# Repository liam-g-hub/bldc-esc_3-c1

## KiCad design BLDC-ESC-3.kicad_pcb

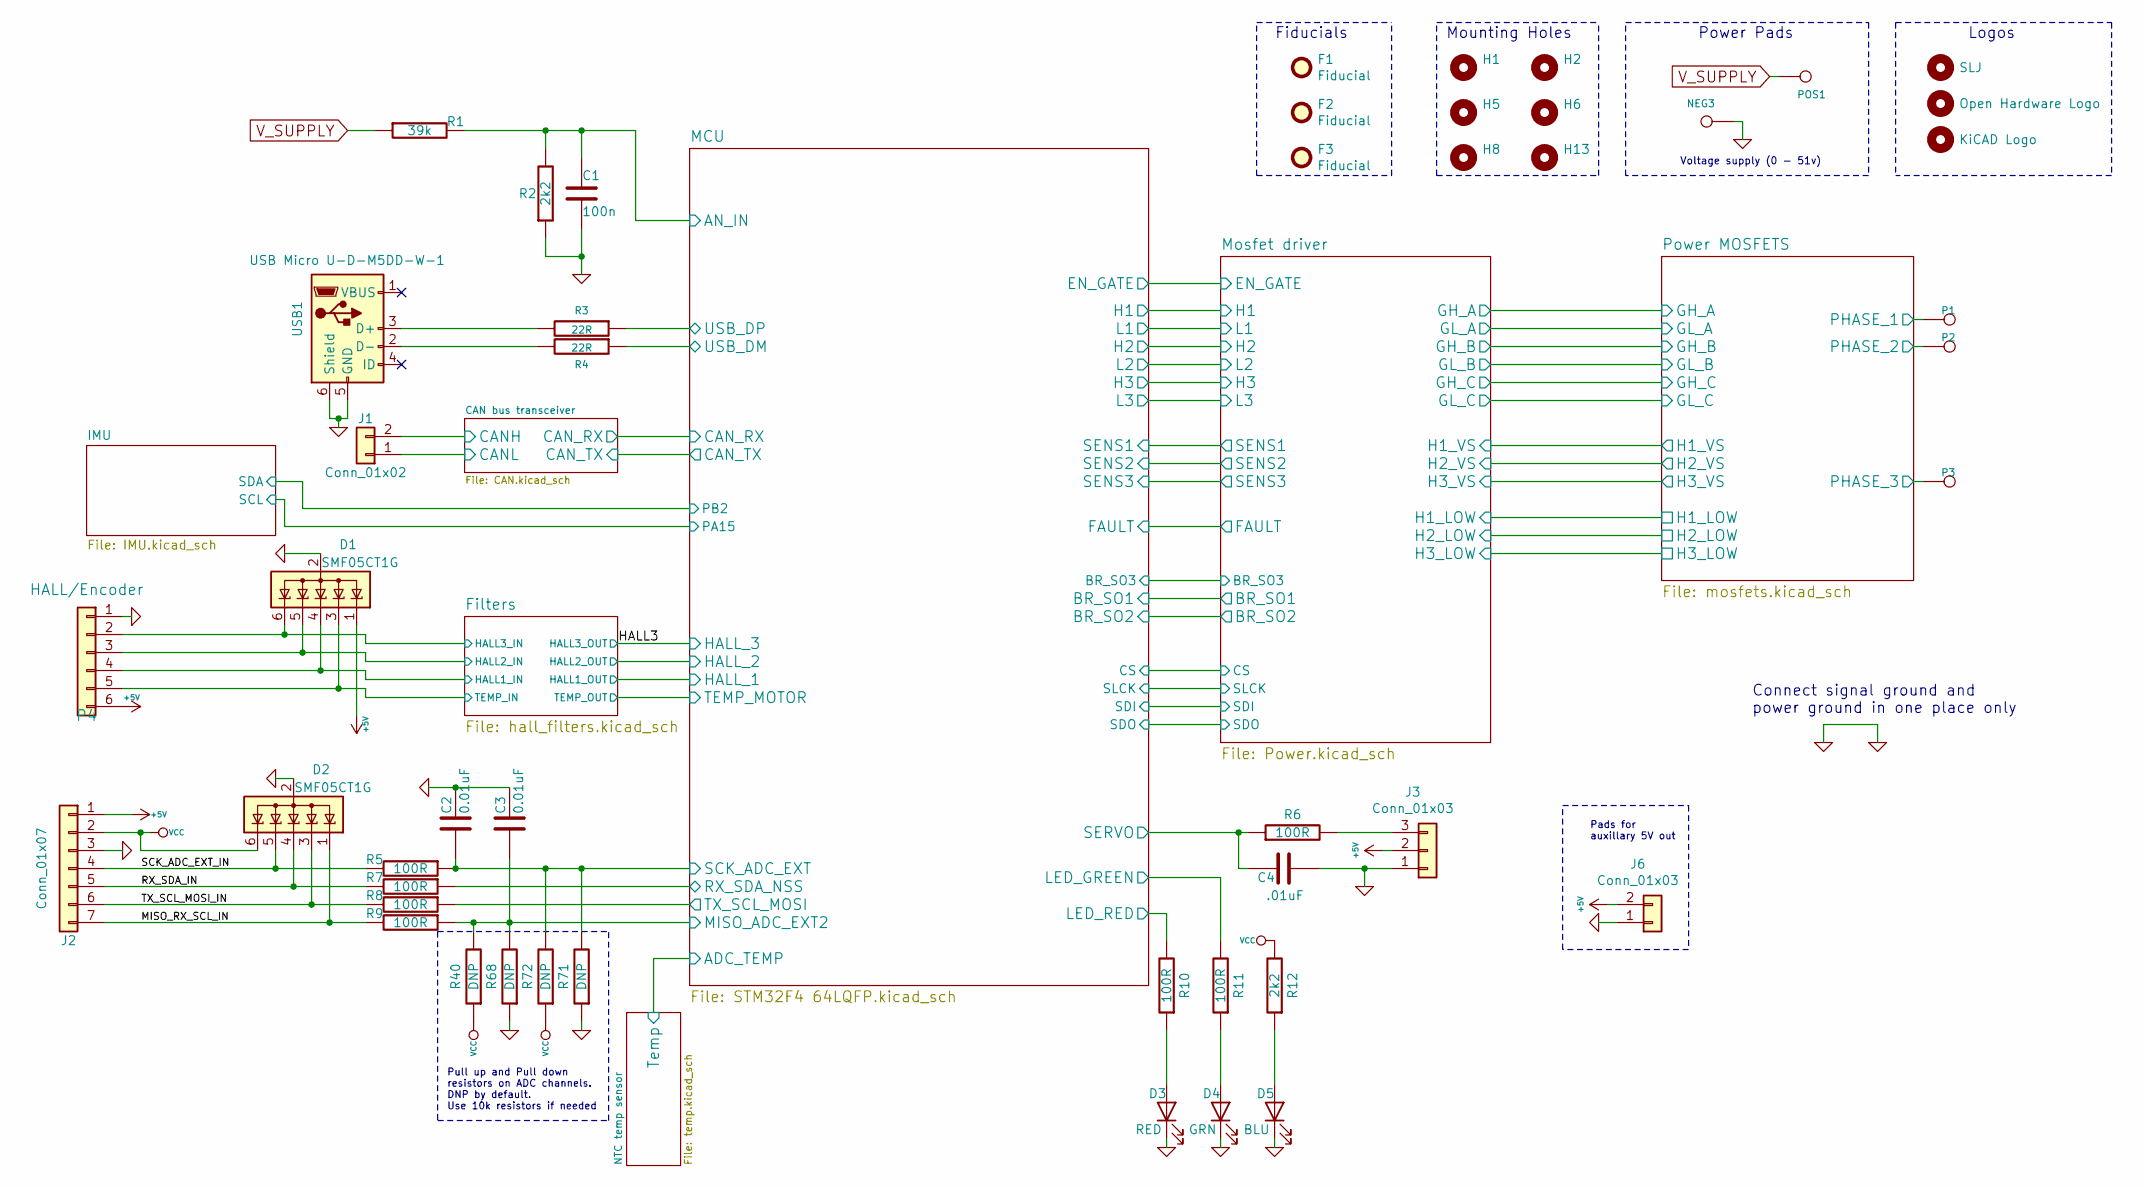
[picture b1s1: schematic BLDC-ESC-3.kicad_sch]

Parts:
C1: 100n; C_0603_1608Metric
C2, C3: 0.01uF; C_0603_1608Metric
C4: .01uF; C_0603_1608Metric
D1, D2: SMF05CT1G; SOT-363_SC-70-6
D3: RED; LED_0603_1608Metric
D4: GRN; LED_0603_1608Metric
D5: BLU; LED_0603_1608Metric
F1, F2, F3: Fiducial; Fiducial_1mm_Dia_2mm_Outer
H1, H2, H5, H6, H8, H13: MountingHole; MountingHole_3.2mm_M3_ISO14580_Pad
H3: SLJ; Sam_J
H4: Open Hardware Logo; OSHW-Logo2_9.8x8mm_SilkScreen
H9: KiCAD Logo; KiCad-Logo2_5mm_SilkScreen
J1: Conn_01x02; JST_PH_B2B-PH-K_1x02_P2.00mm_Vertical
J2: Conn_01x07; JST_PH_B7B-PH-K_1x07_P2.00mm_Vertical
J3: Conn_01x03; JST_PH_B3B-PH-K_1x03_P2.00mm_Vertical_hybrid
J6: Conn_01x03; PinHeader_1x02_P2.54mm_Vertical
NEG3: MOTOR3; 1pin_4mm
P1, P2, P3: MOTOR1; 1pin_4mm
P4: HALL/Encoder; JST_PH_B6B-PH-K_1x06_P2.00mm_Vertical
POS1: POS; 1pin_4mm
R1: 39k; R_0603_1608Metric
R2, R12: 2k2; R_0603_1608Metric
R3, R4: 22R; R_0603_1608Metric
R5, R6, R7, R8, R9, R10, R11: 100R; R_0603_1608Metric
R40, R68, R71, R72: DNP; R_0603_1608Metric
USB1: USB Micro U-D-M5DD-W-1; USB_Micro-B_Wuerth_614105150721_Vertical

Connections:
+5V: D1.1 (K), J2.1, J3.2, J6.2, P4.6; also elsewhere on the board
/CAN bus transceiver/CANH: J1.2; also elsewhere on the board
/CAN bus transceiver/CANL: J1.1; also elsewhere on the board
/Filters/HALL1_IN: D1.4 (K), P4.4; also elsewhere on the board
/Filters/HALL2_IN: D1.5 (K), P4.3; also elsewhere on the board
/Filters/HALL3_IN: D1.6 (K), P4.2; also elsewhere on the board
/Filters/TEMP_IN: D1.3 (K), P4.5; also elsewhere on the board
/MCU/AN_IN: C1.2, R1.2, R2.2; also elsewhere on the board
/MCU/LED_GREEN: R11.2; also elsewhere on the board
/MCU/LED_RED: R10.2; also elsewhere on the board
/MCU/MISO_ADC_EXT2: C3.2, R9.1, R40.2, R68.2; also elsewhere on the board
/MCU/RX_SDA_NSS: R7.1; also elsewhere on the board
/MCU/SCK_ADC_EXT: C2.2, R5.1, R71.2, R72.2; also elsewhere on the board
/MCU/SERVO: C4.2, R6.1; also elsewhere on the board
/MCU/TX_SCL_MOSI: R8.1; also elsewhere on the board
/MCU/USB_DM: R4.1; also elsewhere on the board
/MCU/USB_DP: R3.1; also elsewhere on the board
/MISO_RX_SCL_IN: D2.1 (K), J2.7, R9.2
/Mosfet driver/H1_VS: P1.1; also elsewhere on the board
/Mosfet driver/H2_VS: P2.1; also elsewhere on the board
/Mosfet driver/H3_VS: P3.1; also elsewhere on the board
/RX_SDA_IN: D2.4 (K), J2.5, R7.2
/SCK_ADC_EXT_IN: D2.5 (K), J2.4, R5.2
/TX_SCL_MOSI_IN: D2.3 (K), J2.6, R8.2
GND: C1.1, C2.1, C3.1, C4.1, D1.2 (A), D2.2 (A), D3.1 (K), D4.1 (K), D5.1 (K), J2.3, J3.1, J6.1, NEG3.1, P4.1, R2.1, R68.1, R71.1, USB1.5 (GND), USB1.6 (Shield); also elsewhere on the board
unnamed: D3.2 (A), R10.1
unnamed: D4.2 (A), R11.1
unnamed: D5.2 (A), R12.1
unnamed: J3.3, R6.2
unnamed: R3.2, USB1.3 (D+)
unnamed: R4.2, USB1.2 (D-)
VCC: D2.6 (K), J2.2, R12.2, R40.1, R72.1; also elsewhere on the board
V_SUPPLY: POS1.1, R1.1; also elsewhere on the board

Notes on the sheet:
Pull up and Pull down resistors on ADC channels. DNP by default. Use 10k resistors if needed
Voltage supply (0 - 51v)
Mounting Holes
Power Pads
Pads for auxillary 5V out
Logos
Connect signal ground and power ground in one place only
Fiducials

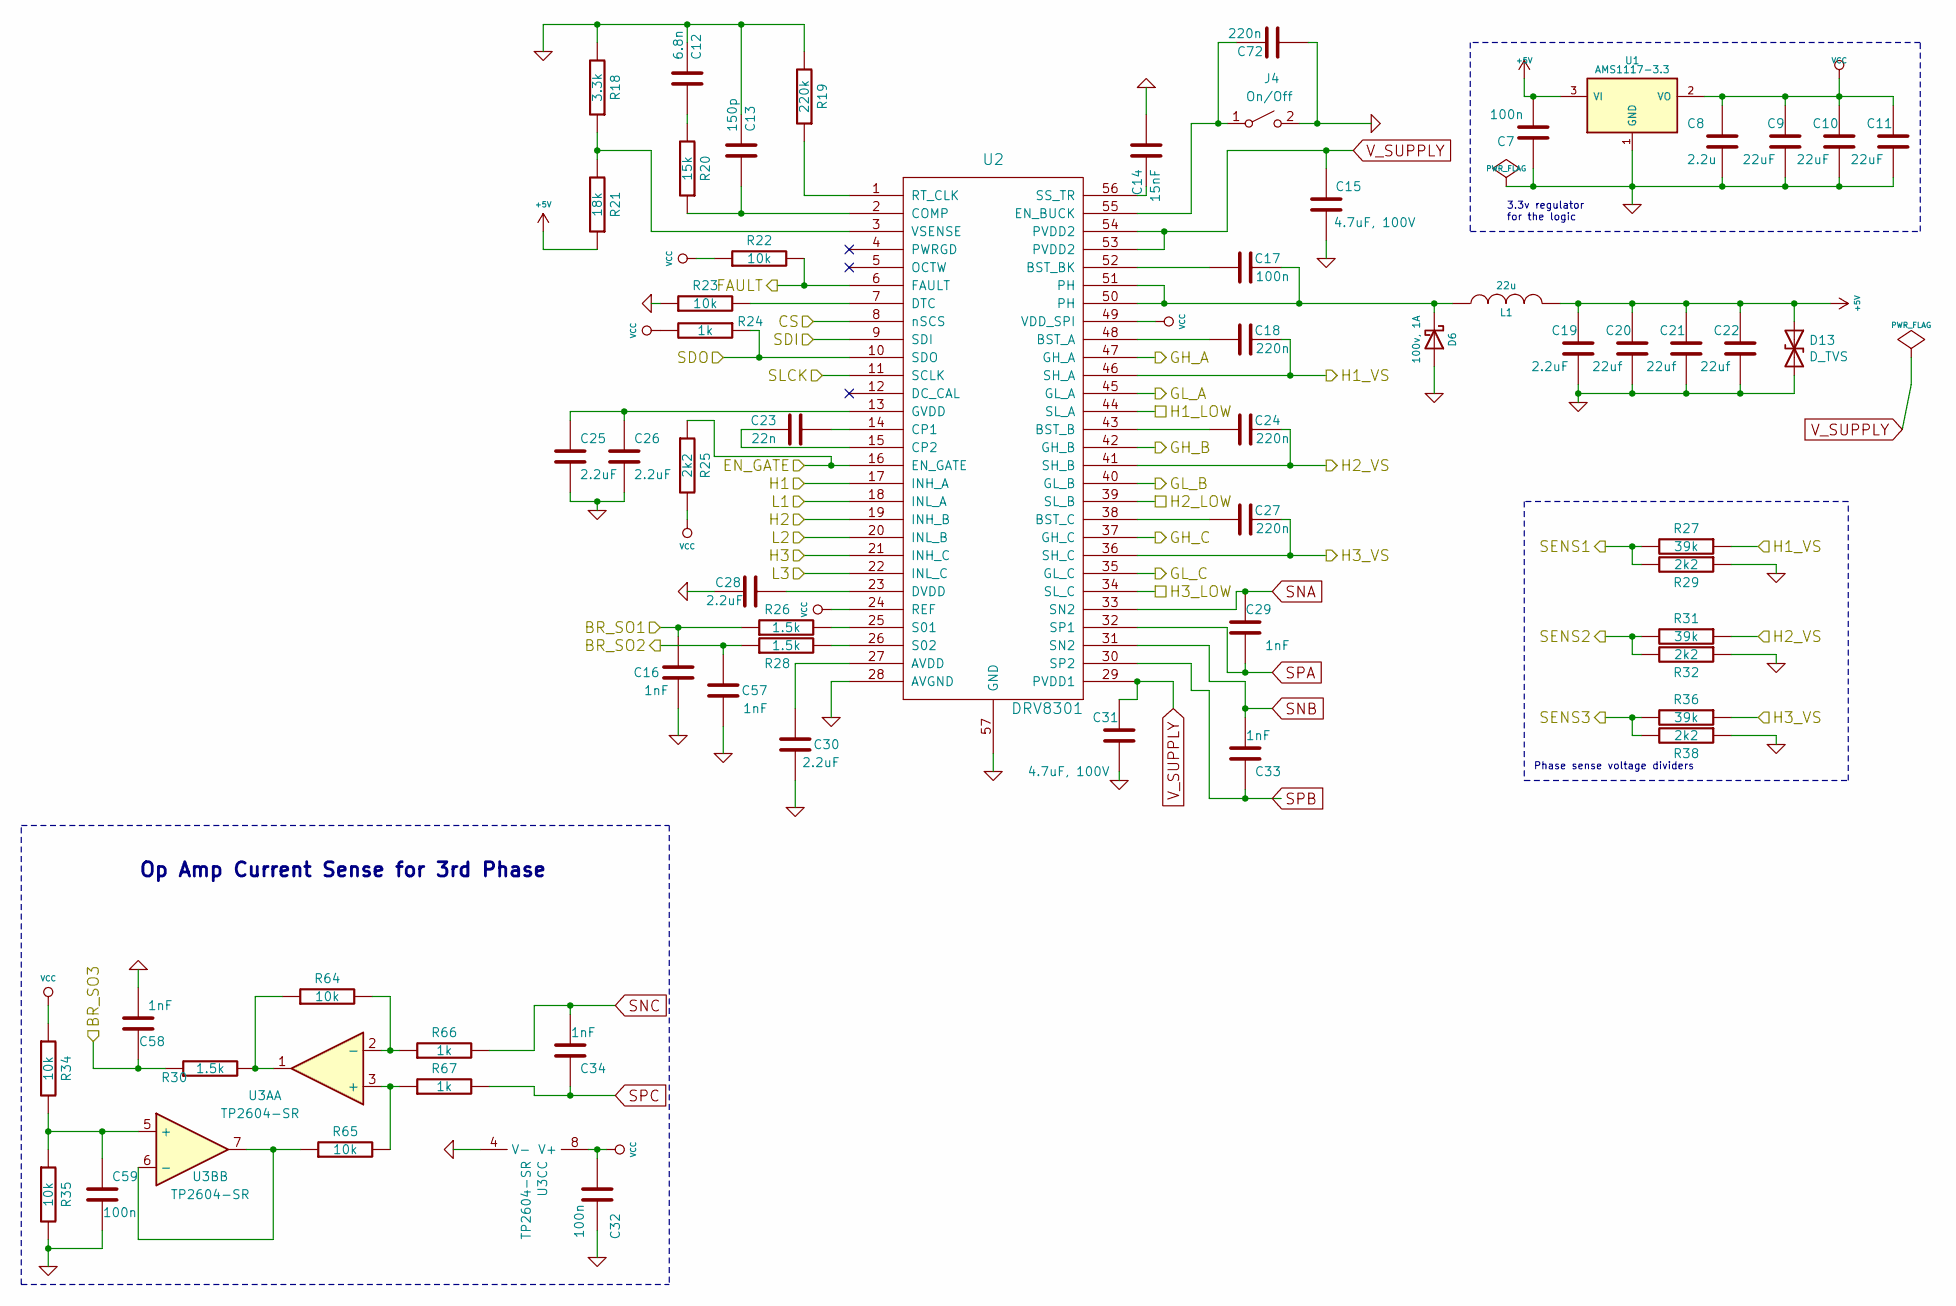
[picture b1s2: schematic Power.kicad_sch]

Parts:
C7, C17, C32, C59: 100n; C_0603_1608Metric
C8: 2.2u; C_0603_1608Metric
C9, C10, C11: 22uF; C_0805_2012Metric
C12: 6.8n; C_0603_1608Metric
C13: 150p; C_0603_1608Metric
C14: 15nF; C_0603_1608Metric
C15, C31: 4.7uF, 100V; C_1210_3225Metric_Pad1.42x2.65mm_HandSolder
C16, C29, C33, C34, C57, C58: 1nF; C_0603_1608Metric
C18, C24, C27, C72: 220n; C_0603_1608Metric
C19, C25, C26, C28, C30: 2.2uF; C_0603_1608Metric
C20, C21, C22: 22uf; C_0805_2012Metric
C23: 22n; C_0603_1608Metric
D6: 100v, 1A; D_SMA
D13: D_TVS; D_SMB
J4: On/Off; JST_PH_B2B-PH-K_1x02_P2.00mm_Vertical
L1: 22u; L_Taiyo-Yuden_NR-60xx_HandSoldering
R18: 3.3k; R_0603_1608Metric
R19: 220k; R_0603_1608Metric
R20: 15k; R_0603_1608Metric
R21: 18k; R_0603_1608Metric
R22, R23, R34, R35, R64, R65: 10k; R_0603_1608Metric
R24, R66, R67: 1k; R_0603_1608Metric
R25, R29, R32, R38: 2k2; R_0603_1608Metric
R26, R28, R30: 1.5k; R_0603_1608Metric
R27, R31, R36: 39k; R_0603_1608Metric
U1: AMS1117-3.3; SOT-223-3_TabPin2
U2: DRV8301; HTSSOP-56-1EP_6.1x14mm_P0.5mm_EP3.61x6.35mm
U3A, U3B, U3C: TP2604-SR; SOIC-8_3.9x4.9mm_P1.27mm

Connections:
+5V: C7.2, C19.2, C20.2, C21.2, C22.2, D13.1 (A1), L1.2, R21.1, U1.3 (VI); also elsewhere on the board
/MCU/BR_SO1: C16.2, R26.1; also elsewhere on the board
/MCU/BR_SO2: C57.2, R28.1; also elsewhere on the board
/MCU/BR_SO3: C58.2, R30.1; also elsewhere on the board
/MCU/CS: U2.8 (nSCS); also elsewhere on the board
/MCU/EN_GATE: R25.1, U2.16 (EN_GATE); also elsewhere on the board
/MCU/FAULT: R22.2, U2.6 (FAULT); also elsewhere on the board
/MCU/H1: U2.17 (INH_A); also elsewhere on the board
/MCU/H2: U2.19 (INH_B); also elsewhere on the board
/MCU/H3: U2.21 (INH_C); also elsewhere on the board
/MCU/L1: U2.18 (INL_A); also elsewhere on the board
/MCU/L2: U2.20 (INL_B); also elsewhere on the board
/MCU/L3: U2.22 (INL_C); also elsewhere on the board
/MCU/SDI: U2.9 (SDI); also elsewhere on the board
/MCU/SDO: R24.1, U2.10 (SDO); also elsewhere on the board
/MCU/SENS1: R27.2, R29.2; also elsewhere on the board
/MCU/SENS2: R31.2, R32.2; also elsewhere on the board
/MCU/SENS3: R36.2, R38.2; also elsewhere on the board
/MCU/SLCK: U2.11 (SCLK); also elsewhere on the board
/Mosfet driver/GH_A: U2.47 (GH_A); also elsewhere on the board
/Mosfet driver/GH_B: U2.42 (GH_B); also elsewhere on the board
/Mosfet driver/GH_C: U2.37 (GH_C); also elsewhere on the board
/Mosfet driver/GL_A: U2.45 (GL_A); also elsewhere on the board
/Mosfet driver/GL_B: U2.40 (GL_B); also elsewhere on the board
/Mosfet driver/GL_C: U2.35 (GL_C); also elsewhere on the board
/Mosfet driver/H1_LOW: U2.44 (SL_A); also elsewhere on the board
/Mosfet driver/H1_VS: C18.2, R27.1, U2.46 (SH_A); also elsewhere on the board
/Mosfet driver/H2_LOW: U2.39 (SL_B); also elsewhere on the board
/Mosfet driver/H2_VS: C24.2, R31.1, U2.41 (SH_B); also elsewhere on the board
/Mosfet driver/H3_LOW: U2.34 (SL_C); also elsewhere on the board
/Mosfet driver/H3_VS: C27.2, R36.1, U2.36 (SH_C); also elsewhere on the board
GND: C7.1, C8.2, C9.1, C10.1, C11.1, C12.1, C13.1, C14.2, C15.1, C16.1, C19.1, C20.1, C21.1, C22.1, C25.2, C26.2, C28.2, C30.1, C31.1, C32.1, C57.1, C58.1, C59.2, C72.1, D6.2 (A), D13.2 (A2), J4.2 (B), R18.2, R19.2, R23.1, R29.1, R32.1, R35.2, R38.1, U1.1 (GND), U2.28 (AVGND), U2.57 (GND), U3C.4 (V-); also elsewhere on the board
unnamed: C12.2, R20.2
unnamed: C13.2, R20.1, U2.2 (COMP)
unnamed: C14.1, U2.56 (SS_TR)
unnamed: C17.1, U2.52 (BST_BK)
unnamed: C17.2, D6.1 (K), L1.1, U2.50 (PH), U2.51 (PH)
unnamed: C18.1, U2.48 (BST_A)
unnamed: C23.1, U2.15 (CP2)
unnamed: C23.2, U2.14 (CP1)
unnamed: C24.1, U2.43 (BST_B)
unnamed: C25.1, C26.1, U2.13 (GVDD)
unnamed: C27.1, U2.38 (BST_C)
unnamed: C28.1, U2.23 (DVDD)
unnamed: C30.2, U2.27 (AVDD)
unnamed 80: C59.1, R34.2, R35.1, U3B.5 (+); also elsewhere on the board
unnamed: C72.2, J4.1 (A), U2.55 (EN_BUCK)
unnamed: R18.1, R21.2, U2.3 (VSENSE)
unnamed: R19.1, U2.1 (RT_CLK)
unnamed: R23.2, U2.7 (DTC)
unnamed: R26.2, U2.25 (S01)
unnamed: R28.2, U2.26 (S02)
unnamed 108: R30.2, R64.1, U3A.1; also elsewhere on the board
unnamed 109: R64.2, R66.1, U3A.2 (-); also elsewhere on the board
unnamed 110: R65.1, U3B.6 (-), U3B.7; also elsewhere on the board
unnamed 111: R65.2, R67.1, U3A.3 (+); also elsewhere on the board
SNA: C29.2, U2.33 (SN2); also elsewhere on the board
SNB: C33.1, U2.31 (SN2); also elsewhere on the board
SNC: C34.1, R66.2; also elsewhere on the board
SPA: C29.1, U2.32 (SP1); also elsewhere on the board
SPB: C33.2, U2.30 (SP2); also elsewhere on the board
SPC: C34.2, R67.2; also elsewhere on the board
VCC: C8.1, C9.2, C10.2, C11.2, C32.2, R22.1, R24.2, R25.2, R34.1, U1.2 (VO), U2.24 (REF), U2.49 (VDD_SPI), U3C.8 (V+); also elsewhere on the board
V_SUPPLY: C15.2, C31.2, U2.29 (PVDD1), U2.53 (PVDD2), U2.54 (PVDD2); also elsewhere on the board

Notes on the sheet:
Phase sense voltage dividers
Op Amp Current Sense for 3rd Phase
3.3v regulator for the logic

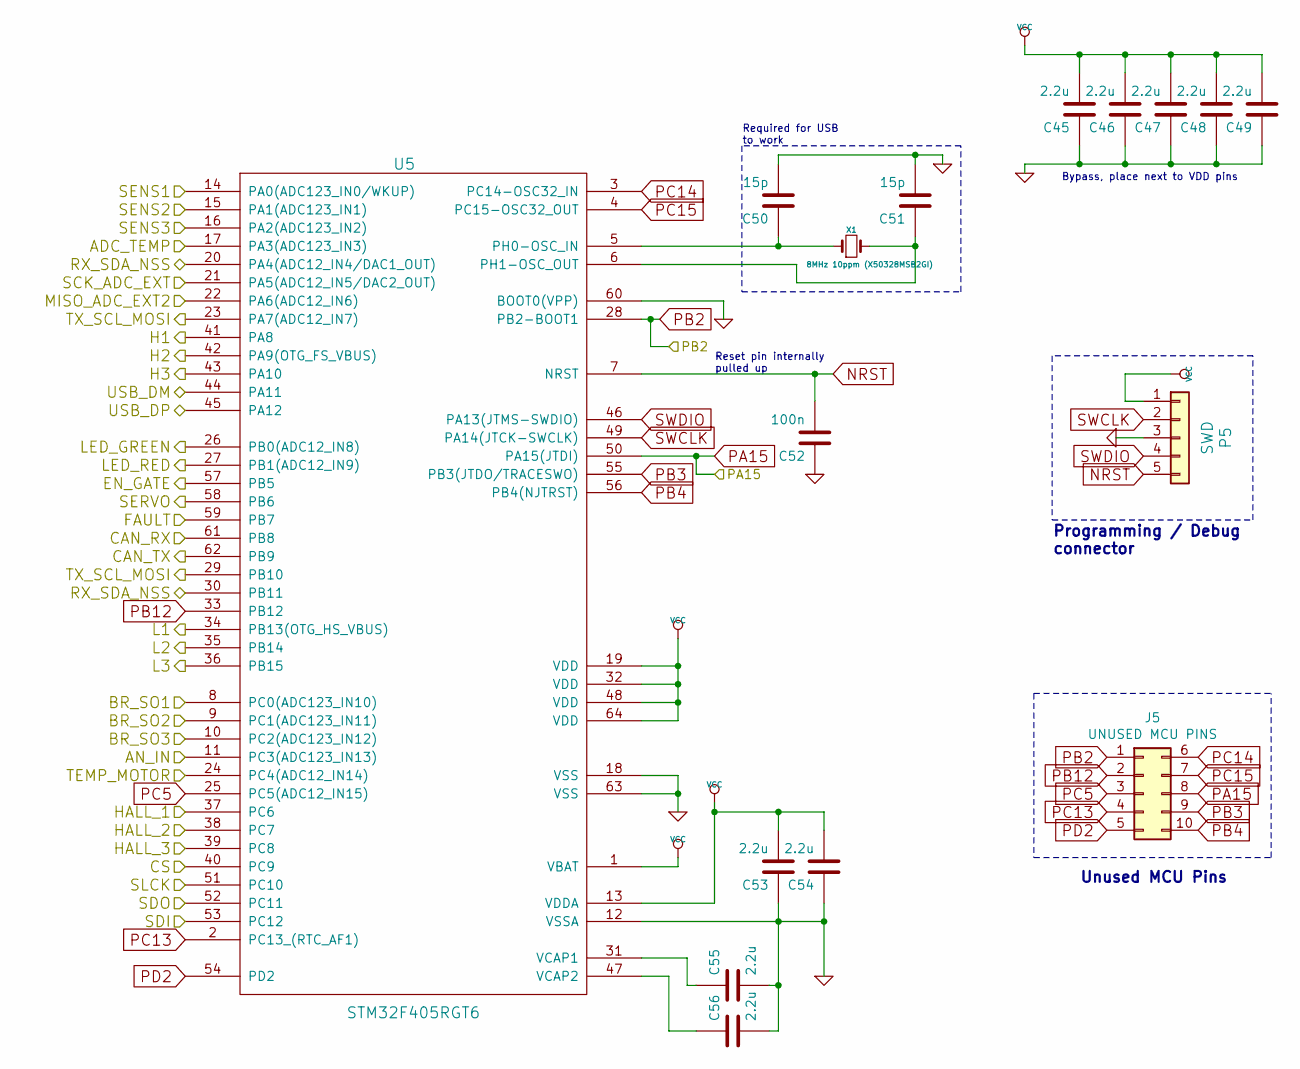
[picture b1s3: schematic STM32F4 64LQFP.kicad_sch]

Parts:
C45, C46, C47, C48, C49, C53, C54, C55, C56: 2.2u; C_0603_1608Metric
C50, C51: 15p; C_0603_1608Metric
C52: 100n; C_0603_1608Metric
J5: UNUSED MCU PINS; PinHeader_2x05_P2.00mm_Vertical
P5: SWD; PinHeader_1x05_P2.54mm_Vertical
U5: STM32F405RGT6; LQFP-64_10x10mm_P0.5mm
X1: 8MHz 10ppm (X50328MSB2GI); Crystal_SMD_5032-2Pin_5.0x3.2mm; mfg# ABM3B-8.0-10-1UT

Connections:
/CAN bus transceiver/CAN_RX: U5.61 (PB8); also elsewhere on the board
/CAN bus transceiver/CAN_TX: U5.62 (PB9); also elsewhere on the board
/Filters/HALL1_OUT: U5.37 (PC6); also elsewhere on the board
/Filters/HALL2_OUT: U5.38 (PC7); also elsewhere on the board
/Filters/TEMP_IN: U5.24 (PC4(ADC12_IN14)); also elsewhere on the board
/HALL3: U5.39 (PC8); also elsewhere on the board
/MCU/ADC_TEMP: U5.17 (PA3(ADC123_IN3)); also elsewhere on the board
/MCU/AN_IN: U5.11 (PC3(ADC123_IN13)); also elsewhere on the board
/MCU/BR_SO1: U5.8 (PC0(ADC123_IN10)); also elsewhere on the board
/MCU/BR_SO2: U5.9 (PC1(ADC123_IN11)); also elsewhere on the board
/MCU/BR_SO3: U5.10 (PC2(ADC123_IN12)); also elsewhere on the board
/MCU/CS: U5.40 (PC9); also elsewhere on the board
/MCU/EN_GATE: U5.57 (PB5); also elsewhere on the board
/MCU/FAULT: U5.59 (PB7); also elsewhere on the board
/MCU/H1: U5.41 (PA8); also elsewhere on the board
/MCU/H2: U5.42 (PA9(OTG_FS_VBUS)); also elsewhere on the board
/MCU/H3: U5.43 (PA10); also elsewhere on the board
/MCU/L1: U5.34 (PB13(OTG_HS_VBUS)); also elsewhere on the board
/MCU/L2: U5.35 (PB14); also elsewhere on the board
/MCU/L3: U5.36 (PB15); also elsewhere on the board
/MCU/LED_GREEN: U5.26 (PB0(ADC12_IN8)); also elsewhere on the board
/MCU/LED_RED: U5.27 (PB1(ADC12_IN9)); also elsewhere on the board
/MCU/MISO_ADC_EXT2: U5.22 (PA6(ADC12_IN6)); also elsewhere on the board
/MCU/RX_SDA_NSS: U5.20 (PA4(ADC12_IN4/DAC1_OUT)), U5.30 (PB11); also elsewhere on the board
/MCU/SCK_ADC_EXT: U5.21 (PA5(ADC12_IN5/DAC2_OUT)); also elsewhere on the board
/MCU/SDI: U5.53 (PC12); also elsewhere on the board
/MCU/SDO: U5.52 (PC11); also elsewhere on the board
/MCU/SENS1: U5.14 (PA0(ADC123_IN0/WKUP)); also elsewhere on the board
/MCU/SENS2: U5.15 (PA1(ADC123_IN1)); also elsewhere on the board
/MCU/SENS3: U5.16 (PA2(ADC123_IN2)); also elsewhere on the board
/MCU/SERVO: U5.58 (PB6); also elsewhere on the board
/MCU/SLCK: U5.51 (PC10); also elsewhere on the board
/MCU/TX_SCL_MOSI: U5.23 (PA7(ADC12_IN7)), U5.29 (PB10); also elsewhere on the board
/MCU/USB_DM: U5.44 (PA11); also elsewhere on the board
/MCU/USB_DP: U5.45 (PA12); also elsewhere on the board
GND: C45.1, C46.1, C47.1, C48.1, C49.1, C50.2, C51.2, C52.1, C53.1, C54.1, C55.2, C56.2, P5.3, U5.12 (VSSA), U5.18 (VSS), U5.60 (BOOT0(VPP)), U5.63 (VSS); also elsewhere on the board
NRST: C52.2, P5.5, U5.7 (NRST)
unnamed: C50.1, U5.5 (PH0-OSC_IN), X1.1
unnamed: C51.1, U5.6 (PH1-OSC_OUT), X1.2
unnamed: C55.1, U5.31 (VCAP1)
unnamed: C56.1, U5.47 (VCAP2)
PA15: J5.8, U5.50 (PA15(JTDI)); also elsewhere on the board
PB2: J5.1, U5.28 (PB2-BOOT1); also elsewhere on the board
PB3: J5.9, U5.55 (PB3(JTDO/TRACESWO))
PB4: J5.10, U5.56 (PB4(NJTRST))
PB12: J5.2, U5.33 (PB12)
PC5: J5.3, U5.25 (PC5(ADC12_IN15))
PC13: J5.4, U5.2 (PC13_(RTC_AF1))
PC14: J5.6, U5.3 (PC14-OSC32_IN)
PC15: J5.7, U5.4 (PC15-OSC32_OUT)
PD2: J5.5, U5.54 (PD2)
SWCLK: P5.2, U5.49 (PA14(JTCK-SWCLK))
SWDIO: P5.4, U5.46 (PA13(JTMS-SWDIO))
VCC: C45.2, C46.2, C47.2, C48.2, C49.2, C53.2, C54.2, P5.1, U5.1 (VBAT), U5.13 (VDDA), U5.19 (VDD), U5.32 (VDD), U5.48 (VDD), U5.64 (VDD); also elsewhere on the board

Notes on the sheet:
Unused MCU Pins
Programming / Debug connector
Reset pin internally pulled up
Bypass, place next to VDD pins
Required for USB to work

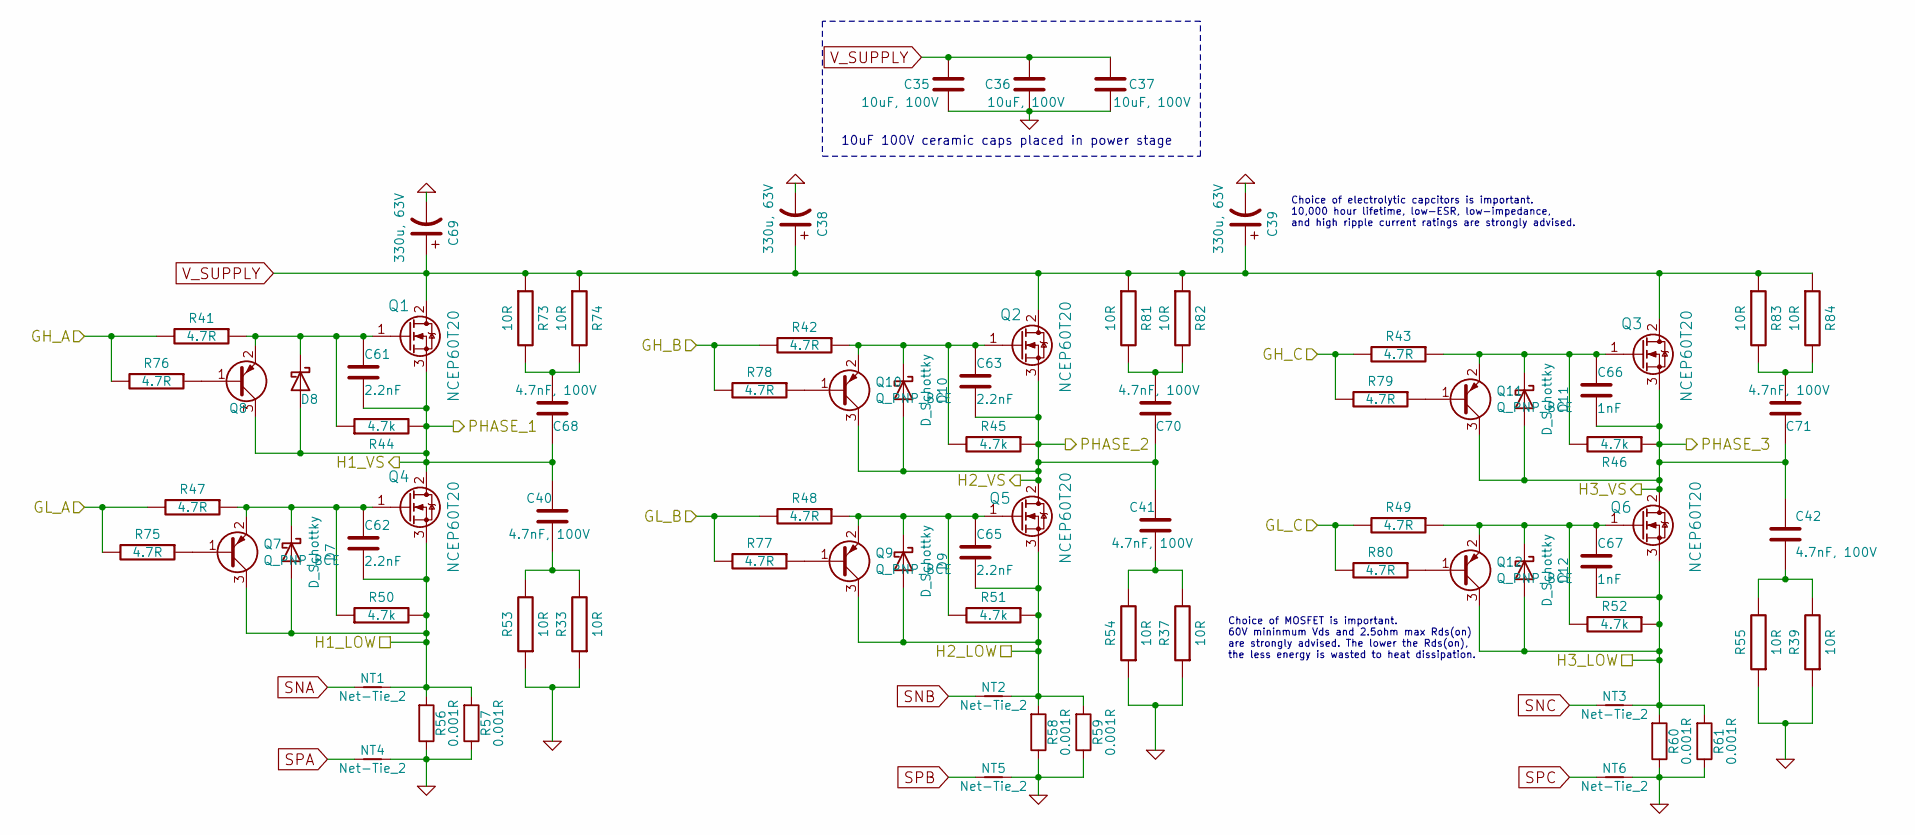
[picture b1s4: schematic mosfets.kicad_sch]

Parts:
C35, C36, C37: 10uF, 100V; C_2220_5650Metric_Pad1.97x5.40mm_HandSolder
C38, C39, C69: 330u, 63V; CP_10x20mm_hor_with_model_mirrored_less_silk
C40, C41, C42, C68, C70, C71: 4.7nF, 100V; C_0805_2012Metric
C61, C62, C63, C65: 2.2nF; C_0603_1608Metric
C66, C67: 1nF; C_0603_1608Metric
D7, D8, D9, D10, D11, D12: D_Schottky; D_SOD-323
NT1, NT2, NT3, NT4, NT5, NT6: Net-Tie_2; NetTie-2_SMD_Pad0.5mm
Q1, Q2, Q3, Q4, Q5, Q6: NCEP60T20; TO-220-3_Horizontal_TabUp_no_hole
Q7, Q8, Q9, Q10, Q11, Q12: Q_PNP_BCE; SOT-23
R33, R37, R39, R53, R54, R55, R73, R74, R81, R82, R83, R84: 10R; R_0805_2012Metric
R41, R42, R43, R47, R48, R49: 4.7R; R_0805_2012Metric
R44, R45, R46, R50, R51, R52: 4.7k; R_0603_1608Metric
R56, R57, R58, R59, R60, R61: 0.001R; R_2512_Yageo_big_pads
R75, R76, R77, R78, R79, R80: 4.7R; R_0603_1608Metric

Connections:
/Mosfet driver/GH_A: R41.2, R76.2; also elsewhere on the board
/Mosfet driver/GH_B: R42.2, R78.2; also elsewhere on the board
/Mosfet driver/GH_C: R43.2, R79.2; also elsewhere on the board
/Mosfet driver/GL_A: R47.2, R75.2; also elsewhere on the board
/Mosfet driver/GL_B: R48.2, R77.2; also elsewhere on the board
/Mosfet driver/GL_C: R49.2, R80.2; also elsewhere on the board
/Mosfet driver/H1_LOW: C62.2, D7.2 (A), NT1.2, Q4.3 (S), Q7.3 (C), R50.2, R56.2, R57.2; also elsewhere on the board
/Mosfet driver/H1_VS: C40.1, C61.2, C68.1, D8.2 (A), Q1.3 (S), Q4.2 (D), Q8.3 (C), R44.2; also elsewhere on the board
/Mosfet driver/H2_LOW: C65.2, D9.2 (A), NT2.2, Q5.3 (S), Q9.3 (C), R51.1, R58.2, R59.2; also elsewhere on the board
/Mosfet driver/H2_VS: C41.1, C63.2, C70.1, D10.2 (A), Q2.3 (S), Q5.2 (D), Q10.3 (C), R45.1; also elsewhere on the board
/Mosfet driver/H3_LOW: C67.2, D12.2 (A), NT3.2, Q6.3 (S), Q12.3 (C), R52.1, R60.2, R61.2; also elsewhere on the board
/Mosfet driver/H3_VS: C42.1, C66.2, C71.1, D11.2 (A), Q3.3 (S), Q6.2 (D), Q11.3 (C), R46.1; also elsewhere on the board
GND: C35.1, C36.1, C37.1, C38.2, C39.2, C69.2, NT4.2, NT5.2, NT6.2, R33.1, R37.1, R39.1, R53.1, R54.1, R55.1, R56.1, R57.1, R58.1, R59.1, R60.1, R61.1; also elsewhere on the board
unnamed: C40.2, R33.2, R53.2
unnamed: C41.2, R37.2, R54.2
unnamed: C42.2, R39.2, R55.2
unnamed: C61.1, D8.1 (K), Q1.1 (G), Q8.2 (E), R41.1, R44.1
unnamed: C62.1, D7.1 (K), Q4.1 (G), Q7.2 (E), R47.1, R50.1
unnamed: C63.1, D10.1 (K), Q2.1 (G), Q10.2 (E), R42.1, R45.2
unnamed: C65.1, D9.1 (K), Q5.1 (G), Q9.2 (E), R48.1, R51.2
unnamed: C66.1, D11.1 (K), Q3.1 (G), Q11.2 (E), R43.1, R46.2
unnamed: C67.1, D12.1 (K), Q6.1 (G), Q12.2 (E), R49.1, R52.2
unnamed: C68.2, R73.2, R74.2
unnamed: C70.2, R81.2, R82.2
unnamed: C71.2, R83.2, R84.2
unnamed: Q7.1 (B), R75.1
unnamed: Q8.1 (B), R76.1
unnamed: Q9.1 (B), R77.1
unnamed: Q10.1 (B), R78.1
unnamed: Q11.1 (B), R79.1
unnamed: Q12.1 (B), R80.1
SNA: NT1.1; also elsewhere on the board
SNB: NT2.1; also elsewhere on the board
SNC: NT3.1; also elsewhere on the board
SPA: NT4.1; also elsewhere on the board
SPB: NT5.1; also elsewhere on the board
SPC: NT6.1; also elsewhere on the board
V_SUPPLY: C35.2, C36.2, C37.2, C38.1, C39.1, C69.1, Q1.2 (D), Q2.2 (D), Q3.2 (D), R73.1, R74.1, R81.1, R82.1, R83.1, R84.1; also elsewhere on the board

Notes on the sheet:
Choice of electrolytic capcitors is important. 10,000 hour lifetime, low-ESR, low-impedance, and high ripple current ratings are strongly advised.
Choice of MOSFET is important. 60V mininmum Vds and 2.5ohm max Rds(on) are strongly advised. The lower the Rds(on), the less energy is wasted to heat dissipation.
10uF 100V ceramic caps placed in power stage

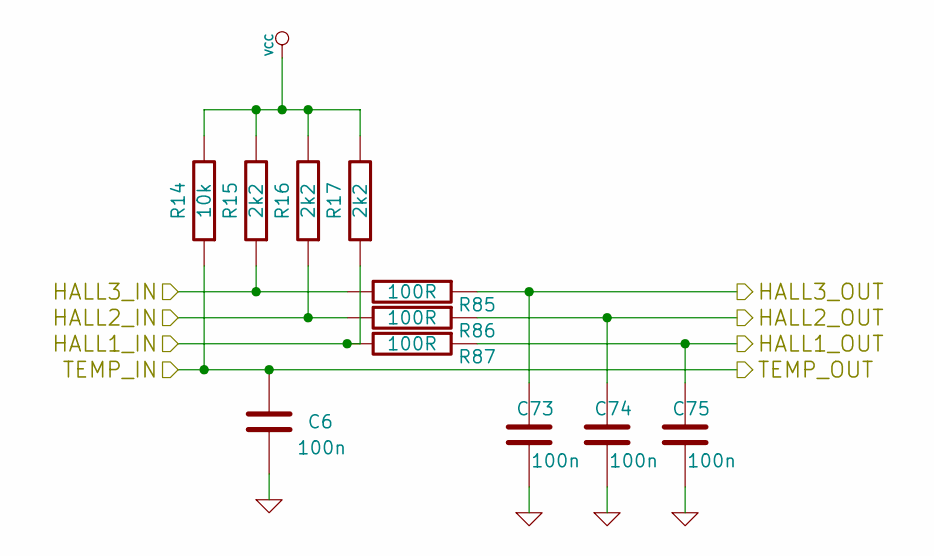
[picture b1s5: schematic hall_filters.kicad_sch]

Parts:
C6, C73, C74, C75: 100n; C_0603_1608Metric
R14: 10k; R_0603_1608Metric
R15, R16, R17: 2k2; R_0603_1608Metric
R85, R86, R87: 100R; R_0603_1608Metric

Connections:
/Filters/HALL1_IN: R17.1, R87.2; also elsewhere on the board
/Filters/HALL1_OUT: C75.2, R87.1; also elsewhere on the board
/Filters/HALL2_IN: R16.1, R86.2; also elsewhere on the board
/Filters/HALL2_OUT: C74.2, R86.1; also elsewhere on the board
/Filters/HALL3_IN: R15.1, R85.2; also elsewhere on the board
/Filters/TEMP_IN: C6.2, R14.1; also elsewhere on the board
/HALL3: C73.2, R85.1; also elsewhere on the board
GND: C6.1, C73.1, C74.1, C75.1; also elsewhere on the board
VCC: R14.2, R15.2, R16.2, R17.2; also elsewhere on the board

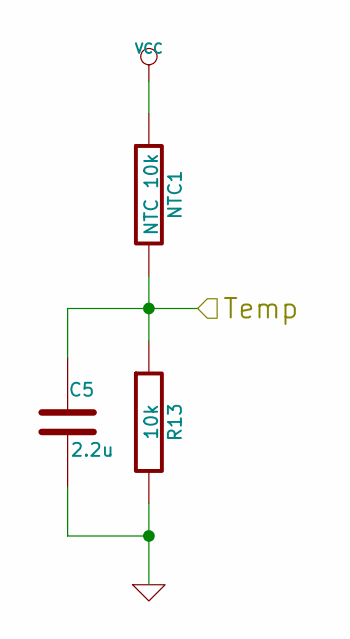
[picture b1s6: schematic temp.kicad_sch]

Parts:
C5: 2.2u; C_0603_1608Metric
NTC1: NTC 10k; R_0603_1608Metric
R13: 10k; R_0603_1608Metric

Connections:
/MCU/ADC_TEMP: C5.1, NTC1.2, R13.1; also elsewhere on the board
GND: C5.2, R13.2; also elsewhere on the board
VCC: NTC1.1; also elsewhere on the board

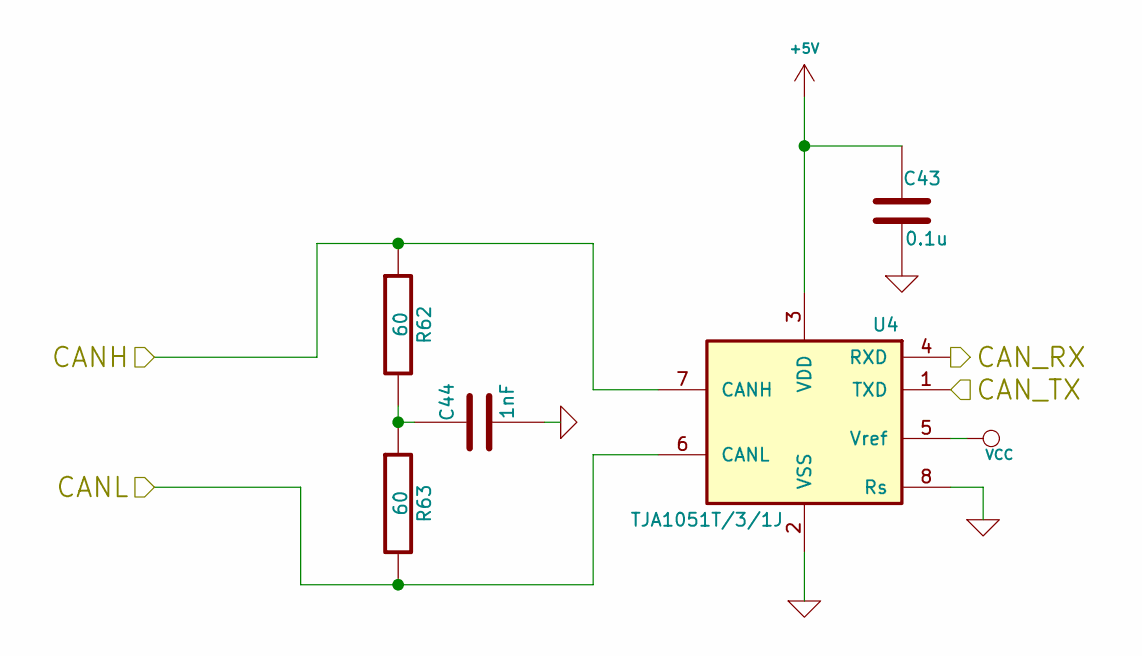
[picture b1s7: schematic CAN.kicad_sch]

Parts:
C43: 0.1u; C_0603_1608Metric
C44: 1nF; C_0603_1608Metric
R62, R63: 60; R_0603_1608Metric
U4: TJA1051T/3/1J; SOIC-8_3.9x4.9mm_P1.27mm

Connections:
+5V: C43.1, U4.3 (VDD); also elsewhere on the board
/CAN bus transceiver/CANH: R62.1, U4.7 (CANH); also elsewhere on the board
/CAN bus transceiver/CANL: R63.2, U4.6 (CANL); also elsewhere on the board
/CAN bus transceiver/CAN_RX: U4.4 (RXD); also elsewhere on the board
/CAN bus transceiver/CAN_TX: U4.1 (TXD); also elsewhere on the board
GND: C43.2, C44.2, U4.2 (VSS), U4.8 (Rs); also elsewhere on the board
unnamed: C44.1, R62.2, R63.1
VCC: U4.5 (Vref); also elsewhere on the board

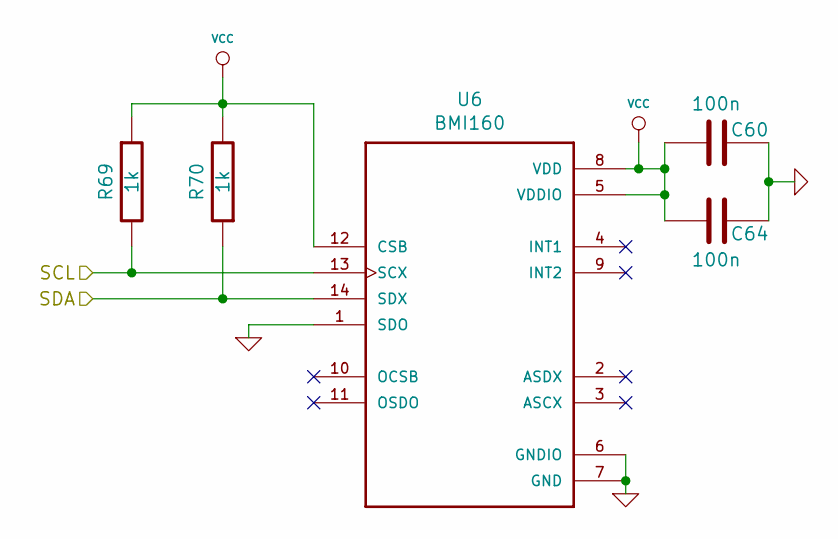
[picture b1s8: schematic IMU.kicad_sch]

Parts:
C60, C64: 100n; C_0603_1608Metric
R69, R70: 1k; R_0603_1608Metric
U6: BMI160; Bosch_LGA-14_3x2.5mm_P0.5mm

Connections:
GND: C60.1, C64.1, U6.1 (SDO), U6.6 (GNDIO), U6.7 (GND); also elsewhere on the board
PA15: R69.2, U6.13 (SCX); also elsewhere on the board
PB2: R70.1, U6.14 (SDX); also elsewhere on the board
VCC: C60.2, C64.2, R69.1, R70.2, U6.5 (VDDIO), U6.8 (VDD), U6.12 (CSB); also elsewhere on the board

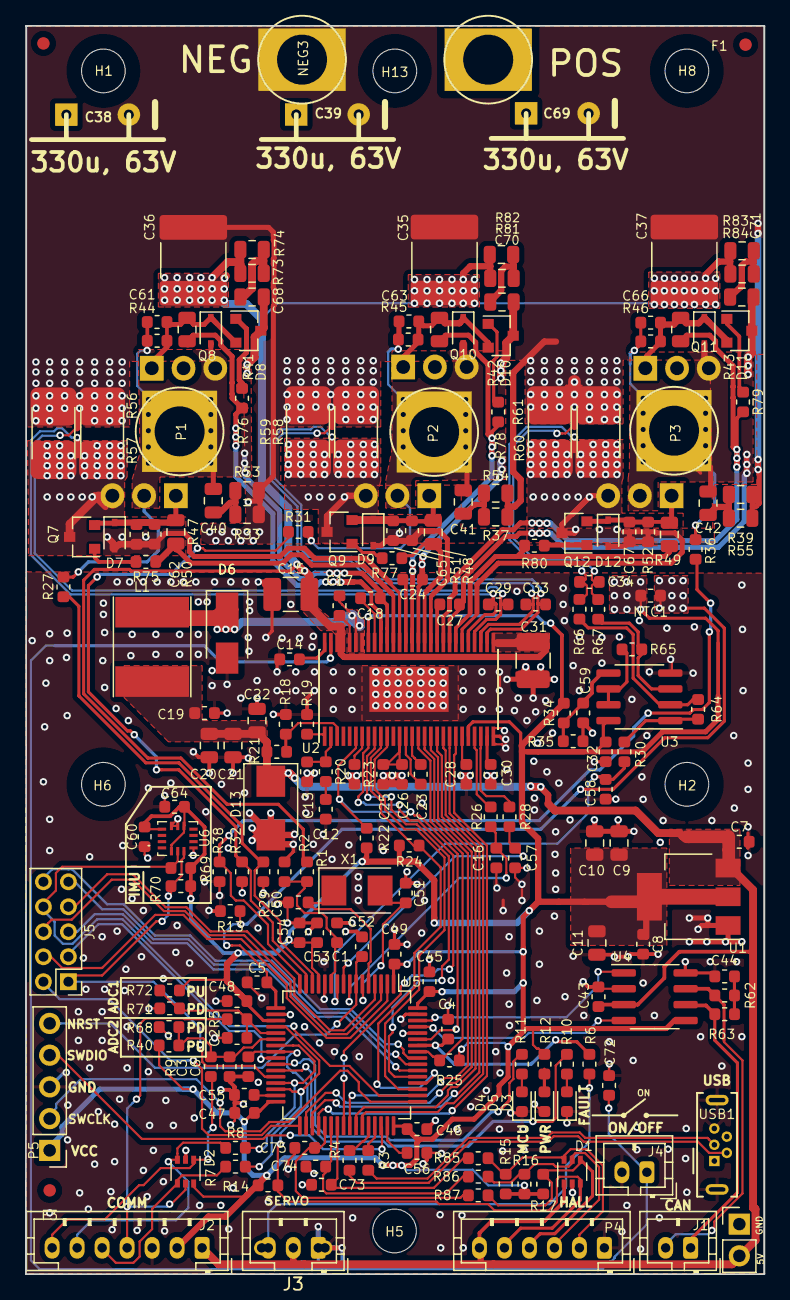
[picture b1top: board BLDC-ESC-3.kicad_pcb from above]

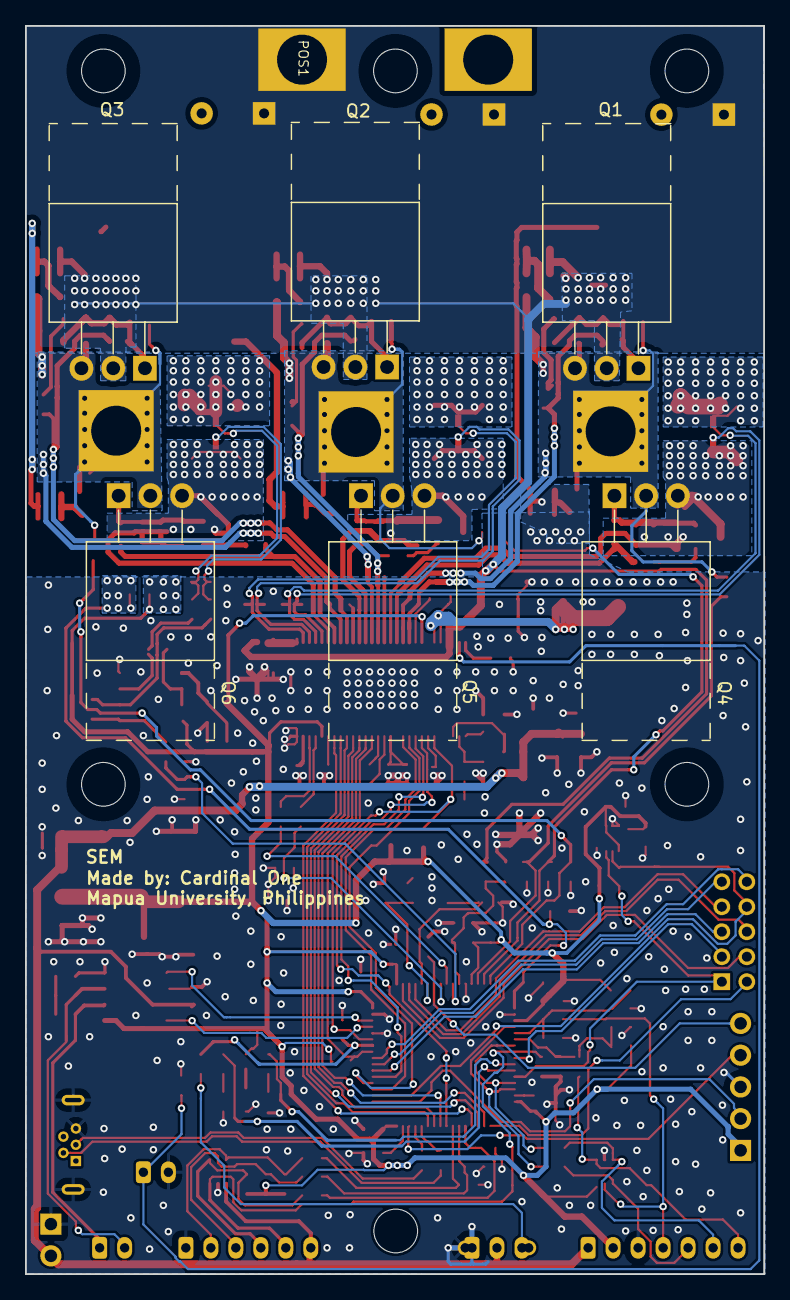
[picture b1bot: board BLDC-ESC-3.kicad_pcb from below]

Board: 2 copper layers, 59.1 x 99.9 mm, 225 parts (6 on the bottom side), 132 nets.

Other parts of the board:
U3: TP2604-SR; SOIC-8_3.9x4.9mm_P1.27mm

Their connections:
GND: U3.4; also elsewhere on the board
unnamed 80: U3.5; also elsewhere on the board
unnamed 108: U3.1; also elsewhere on the board
unnamed 109: U3.2; also elsewhere on the board
unnamed 110: U3.6, U3.7; also elsewhere on the board
unnamed 111: U3.3; also elsewhere on the board
VCC: U3.8; also elsewhere on the board

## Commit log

2025-09-13 3D directory added
2025-09-14 pdf schematic upload
